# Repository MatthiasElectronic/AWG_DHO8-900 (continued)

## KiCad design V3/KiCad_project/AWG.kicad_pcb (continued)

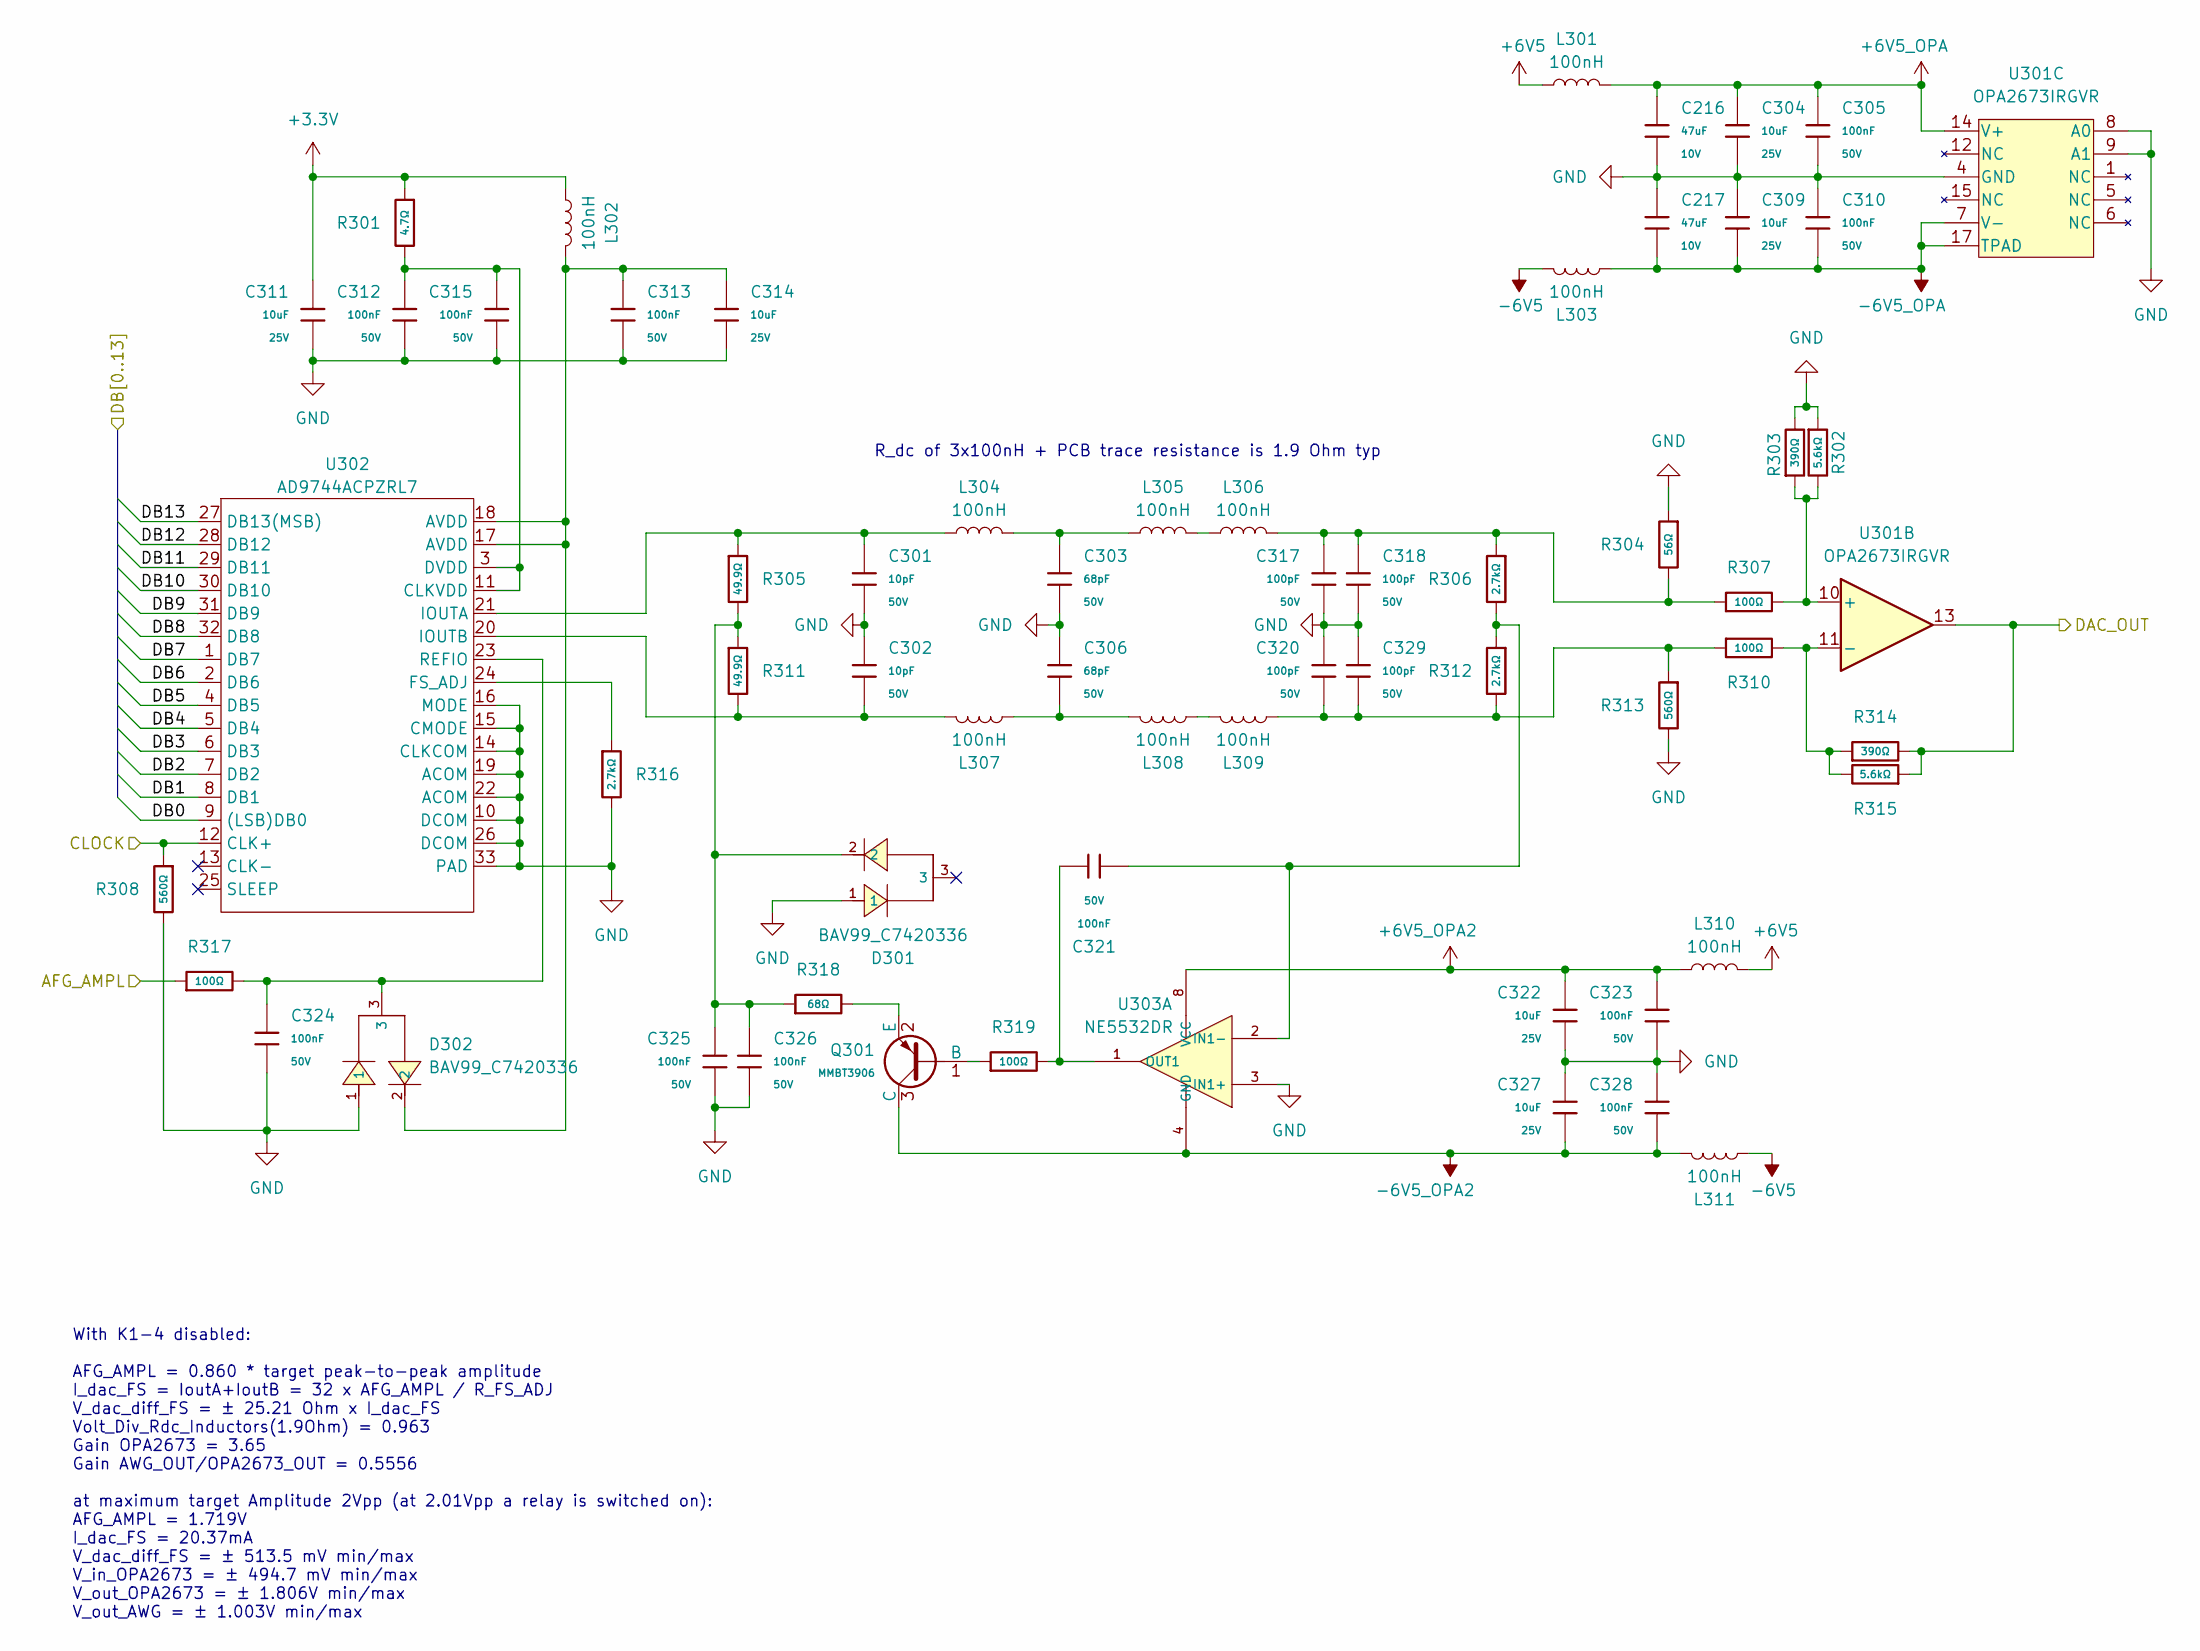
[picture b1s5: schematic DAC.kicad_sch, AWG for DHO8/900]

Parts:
C216, C217: 47uF; C_1206; Voltage Rated 10V; Tolerance ±20%; Part CL31A476MPHNNNE; LCSC C96123
C301, C302: 10pF; C_0603; Voltage Rated 50V; Tolerance ±5%; Part CL10C100JB8NNNC; LCSC C1634
C303, C306: 68pF; C_0603; Voltage Rated 50V; Tolerance ±5%; Part CL10C680JB8NNNC; LCSC C28262
C304, C309, C311, C314, C322, C327: 10uF; C_0805; Voltage Rated 25V; Tolerance ±10%; Part CL21A106KAYNNNE; LCSC C15850
C305, C310, C312, C313, C315, C321, C323, C324, C325, C326, C328: 100nF; C_0603; Voltage Rated 50V; Tolerance ±10%; Part CC0603KRX7R9BB104; LCSC C14663
C317, C318, C320, C329: 100pF; C_0603; Voltage Rated 50V; Tolerance ±5%; Part CL10C101JB8NNNC; LCSC C14858
D301, D302: BAV99_C7420336; SOT-23-3_L2.9-W1.3-P1.90-LS2.4-BR; Reverse Voltage (Vr) 100V; Forward Voltage (Vf@If) 1.25V@150mA; Part BAV99; LCSC C7420336
L301, L302, L303, L304, L305, L306, L307, L308, L309, L310, L311: 100nH; L_0603; LCSC C98088
Q301: MMBT3906; Q_SOT-23; Part MMBT3906; LCSC C7420354
R301: 4.7Ω; R_0603; Overload Voltage (Max) 75V; Tolerance ±1%; Part 0603WAF470KT5E; LCSC C23164
R302, R315: 5.6kΩ; R_0603; Overload Voltage (Max) 75V; Tolerance ±1%; Part 0603WAF5601T5E; LCSC C23189
R303, R314: 390Ω; R_0603; Overload Voltage (Max) 75V; Tolerance ±1%; Part 0603WAF3900T5E; LCSC C23151
R304: 56Ω; R_0603; Overload Voltage (Max) 75V; Tolerance ±1%; Part 0603WAF560JT5E; LCSC C25196
R305, R311: 49.9Ω; R_0603; Overload Voltage (Max) 75V; Tolerance ±1%; Part 0603WAF499JT5E; LCSC C23185
R306, R312, R316: 2.7kΩ; R_0603; Overload Voltage (Max) 75V; Tolerance ±1%; Part 0603WAF2701T5E; LCSC C13167
R307, R310, R317, R319: 100Ω; R_0603; Overload Voltage (Max) 75V; Tolerance ±1%; Part 0603WAF1000T5E; LCSC C22775
R308, R313: 560Ω; R_0603; Overload Voltage (Max) 75V; Tolerance ±1%; Part 0603WAF5600T5E; LCSC C23204
R318: 68Ω; R_0603; Overload Voltage (Max) 75V; Tolerance ±1%; Part 0603WAF680JT5E; LCSC C27592
U301: OPA2673IRGVR; Texas_RSA_VQFN-16-1EP_4x4mm_P0.65mm_EP2.7x2.7mm; LCSC C1848168
U302: AD9744ACPZRL7; LFCSP-32_L5.0-W5.0-P0.50-BL-EP3.1; Manufacturer Part AD9744ACPZRL7; LCSC Part Name AD9744ACPZRL7
U303: NE5532DR; SOIC-8_L4.9-W3.9-P1.27-LS6.0-BL; Part NE5532DR; LCSC C7426

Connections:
+3.3V: C311.1, L302.1, R301.1; also elsewhere on the board
+6V5: L301.2, L310.1; also elsewhere on the board
+6V5_OPA: C216.2, C304.1, C305.1, L301.1, U301.14 (V+); also elsewhere on the board
+6V5_OPA2: C322.1, C323.1, L310.2, U303.8 (VCC); also elsewhere on the board
-6V5: L303.2, L311.1; also elsewhere on the board
-6V5_OPA: C217.1, C309.2, C310.2, L303.1, U301.7 (V-), U301.17 (TPAD); also elsewhere on the board
-6V5_OPA2: C327.2, C328.2, L311.2, Q301.3 (C), U303.4 (GND); also elsewhere on the board
/AFG_AMPL: R317.1; also elsewhere on the board
/CLOCK: R308.1, U302.12 (CLK+); also elsewhere on the board
/DAC/DAC_OUT: R314.2, R315.1, U301.13; also elsewhere on the board
/DB0: U302.9 ((LSB)DB0); also elsewhere on the board
/DB1: U302.8 (DB1); also elsewhere on the board
/DB2: U302.7 (DB2); also elsewhere on the board
/DB3: U302.6 (DB3); also elsewhere on the board
/DB4: U302.5 (DB4); also elsewhere on the board
/DB5: U302.4 (DB5); also elsewhere on the board
/DB6: U302.2 (DB6); also elsewhere on the board
/DB7: U302.1 (DB7); also elsewhere on the board
/DB8: U302.32 (DB8); also elsewhere on the board
/DB9: U302.31 (DB9); also elsewhere on the board
/DB10: U302.30 (DB10); also elsewhere on the board
/DB11: U302.29 (DB11); also elsewhere on the board
/DB12: U302.28 (DB12); also elsewhere on the board
/DB13: U302.27 (DB13(MSB)); also elsewhere on the board
GND: C216.1, C217.2, C301.2, C302.1, C303.2, C304.2, C305.2, C306.1, C309.1, C310.1, C311.2, C312.2, C313.2, C314.2, C315.2, C317.2, C318.2, C320.1, C322.2, C323.2, C324.2, C325.2, C326.2, C327.1, C328.1, C329.1, D301.1, D302.1, R302.1, R303.2, R304.1, R308.2, R313.2, R316.2, U301.4 (GND), U301.8 (A0), U301.9 (A1), U302.10 (DCOM), U302.14 (CLKCOM), U302.15 (CMODE), U302.16 (MODE), U302.19 (ACOM), U302.22 (ACOM), U302.26 (DCOM), U302.33 (PAD), U303.3 (IN1+); also elsewhere on the board
unnamed: C303.1, L304.2, L305.1
unnamed: C306.2, L307.2, L308.1
unnamed: C313.1, C314.1, D302.2, L302.2, U302.17 (AVDD), U302.18 (AVDD)
unnamed: C317.1, C318.1, L306.2, R304.2, R306.1, R307.1
unnamed: C320.2, C329.2, L309.2, R310.1, R312.2, R313.1
unnamed: C325.1, C326.1, D301.2, R305.2, R311.1, R318.1
unnamed: L305.2, L306.1
unnamed: L308.2, L309.1
unnamed: Q301.1 (B), R319.1
unnamed: Q301.2 (E), R318.2
unnamed: R302.2, R303.1, R307.2, U301.10 (+)
unnamed: R310.2, R314.1, R315.2, U301.11 (-)
unnamed: C312.1, C315.1, R301.2, U302.3 (DVDD), U302.11 (CLKVDD)
unnamed: R316.1, U302.24 (FS_ADJ)
unnamed: C301.1, L304.1, R305.1, U302.21 (IOUTA)
unnamed: C302.2, L307.1, R311.2, U302.20 (IOUTB)
unnamed: C324.1, D302.3, R317.2, U302.23 (REFIO)
unnamed: C321.2, R306.2, R312.1, U303.2 (IN1-)
unnamed: C321.1, R319.2, U303.1 (OUT1)

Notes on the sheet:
With K1-4 disabled: AFG_AMPL = 0.860 * target peak-to-peak amplitude I_dac_FS = IoutA+IoutB = 32 x AFG_AMPL / R_FS_ADJ V_dac_diff_FS = ± 25.21 Ohm x I_dac_FS Volt_Div_Rdc_Inductors(1.9Ohm) = 0.963 Gain OPA2673 = 3.65 Gain AWG_OUT/OPA2673_OUT = 0.5556 at maximum target Amplitude 2Vpp (at 2.01Vpp a r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
R_dc of 3x100nH + PCB trace resistance is 1.9 Ohm typ

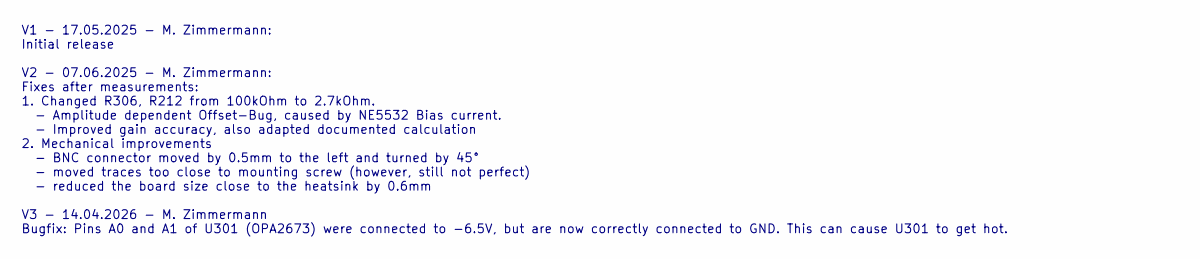
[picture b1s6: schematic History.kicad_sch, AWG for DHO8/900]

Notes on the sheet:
V1 - 17.05.2025 - M. Zimmermann: Initial release V2 - 07.06.2025 - M. Zimmermann: Fixes after measurements: 1. Changed R306, R212 from 100kOhm to 2.7kOhm. - Amplitude dependent Offset-Bug, caused by NE5532 Bias current. - Improved gain accuracy, also adapted documented calculation 2. Mechanical imp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

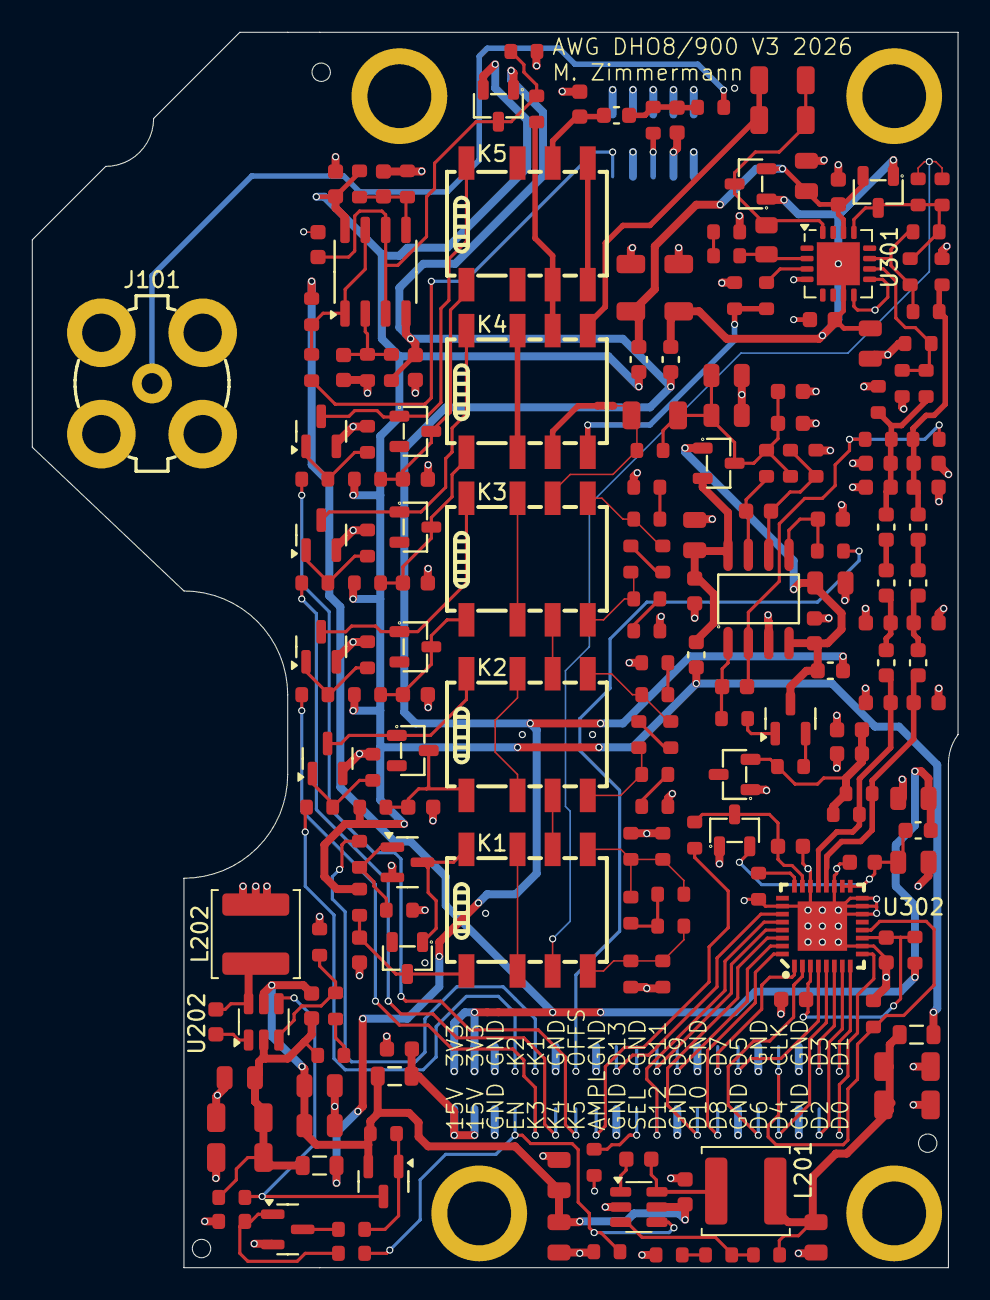
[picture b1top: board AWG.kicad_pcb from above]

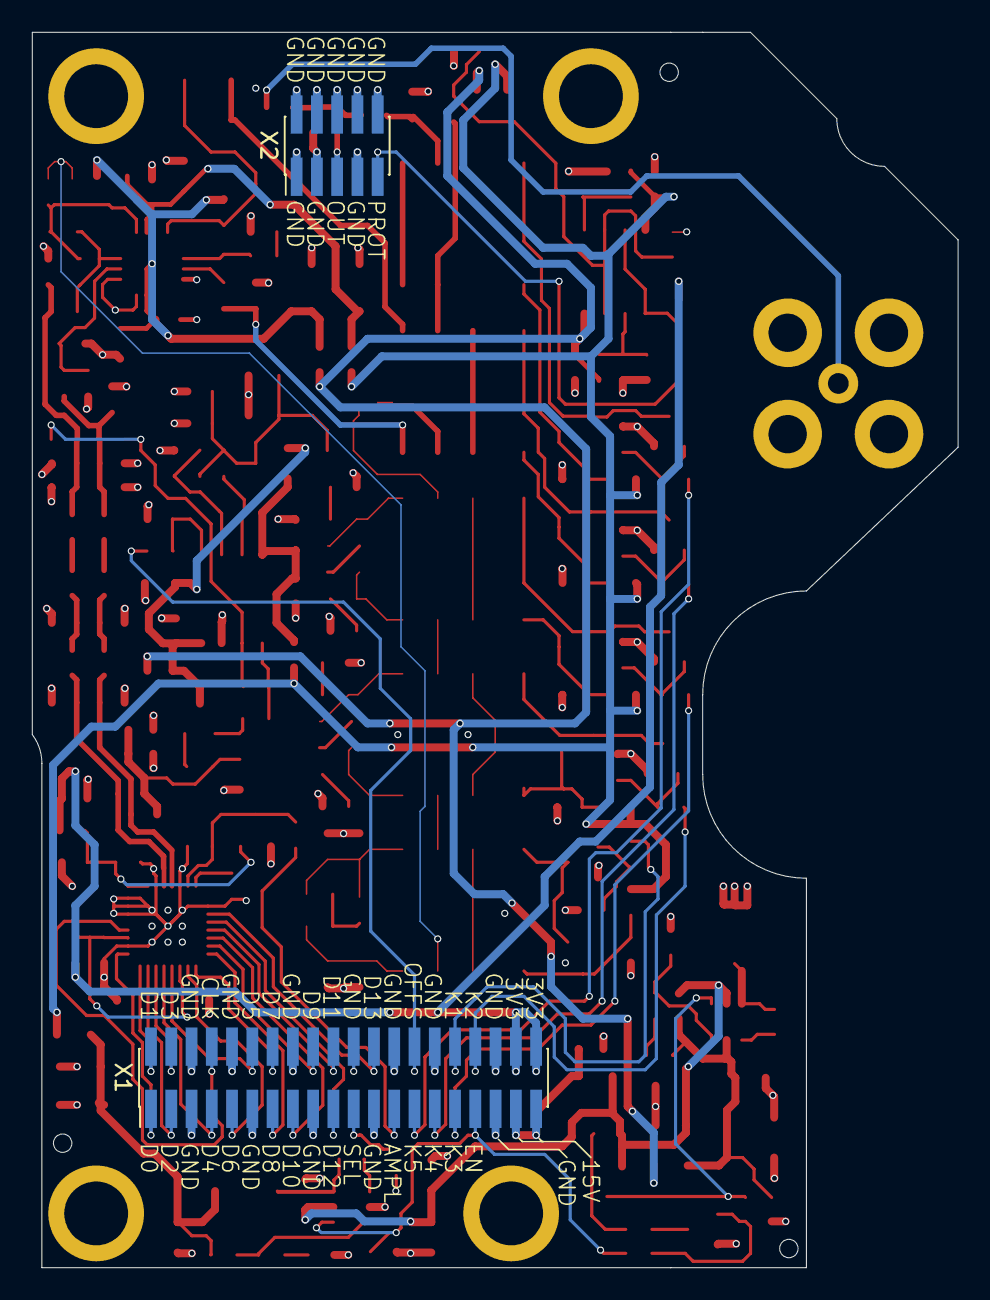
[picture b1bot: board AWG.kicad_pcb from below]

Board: 4 copper layers, 58.0 x 77.4 mm, 208 parts (2 on the bottom side), 126 nets.

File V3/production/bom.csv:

Designator,Footprint,Quantity,Value,LCSC Part #
"C201, C202, C203, C209, C210, C305, C310, C312, C313, C315, C321, C323, C324, C325, C326, C328, C401, C404, C405, C501, C505",C_0603,21,100nF,C14663
"C204, C205, C206, C211, C212, C213, C304, C309, C311, C314, C322, C327, C402, C403",C_0805,14,10uF,C15850
"C207, C208, C214, C215, C216, C217",C_1206,6,47uF,C96123
"C301, C302",C_0603,2,10pF,C1634
"C303, C306",C_0603,2,68pF,C28262
"C317, C318, C320, C329",C_0603,4,100pF,C14858
"C406, C409, C410, C411, C412, C413, C502, C503",C_0603,8,1uF,C15849
"C407, C408, C504",C_0603,3,47pF,C1671
"D301, D302, D401, D402, D403, D404, D405, D406, D407, D408, D501",SOT-23-3_L2.9-W1.3-P1.90-LS2.4-BR,11,BAV99_C7420336,C7420336
"FB201, FB202, FB203",FB_0805,3,~,C1015
J101,BNC_Amphenol_ICC 031-5329-51RFX,1,BNC_Amphenol_ICC 031-5329-51RFX,C5443992
"K1, K2, K3, K4, K5",RELAY-SMD_G6K-2F-X-XX,5,~,C47190
"L201, L202",L_APV_ANR5045,2,22uH,C440232
"L301, L302, L303, L304, L305, L306, L307, L308, L309, L310, L311, L401",L_0603,12,100nH,C98088
"Q201, Q301",Q_SOT-23,2,MMBT3906,C7420354
"Q202, Q401, Q402, Q403, Q404, Q405",Q_SOT-23,6,BC846B,C20069134
"R101, R504",R_0603,2,1kΩ,C21190
R103,R_0603,1,0Ω,C21189
"R201, R207",R_0603,2,24kΩ,C23352
"R202, R205, R206, R210, R212, R435, R436, R440, R441, R442",R_0603,10,22kΩ,C31850
"R203, R208, R209, R408, R433, R434, R437, R438, R439, R502, R507",R_0603,11,3.3kΩ,C22978
"R204, R211, R318, R443, R444, R445, R446, R447",R_0603,8,68Ω,C27592
"R301, R406",R_0603,2,4.7Ω,C23164
"R302, R315",R_0603,2,5.6kΩ,C23189
"R303, R314, R427, R428",R_0603,4,390Ω,C23151
"R304, R430, R431",R_0603,3,56Ω,C25196
"R305, R311",R_0603,2,49.9Ω,C23185
"R306, R312, R316",R_0603,3,2.7kΩ,C13167
"R307, R310, R317, R319, R422, R423, R424, R425",R_0603,8,100Ω,C22775
"R308, R313",R_0603,2,560Ω,C23204
"R401, R419, R420",R_0603,3,4.7kΩ,C23162
"R402, R405, R409",R_0603,3,15Ω,C22810
"R403, R505, R508",R_0603,3,100kΩ,C25803
R404,R_0805,1,270Ω,C17590
R407,R_0603,1,4.3kΩ,C23159
"R410, R413",R_1206,2,100Ω,C17901
"R414, R415, R416, R417",R_0603,4,10Ω,C22859
"R418, R421, R432, R460",R_0603,4,180Ω,C22828
R426,R_0603,1,47Ω,C23182
R429,R_0603,1,6.8kΩ,C23212
R455,R_0603,1,82Ω,C23255
R457,R_1206,1,120Ω,C17909
R458,R_0603,1,1.8kΩ,C4177
"R501, R506",R_0603,2,3.9kΩ,C23018
R503,R_0603,1,5.1kΩ,C23186
"U201, U202",SOT-23-6,2,LMR54406FDBVR,C3193129
U301,Texas_RSA_VQFN-16-1EP_4x4mm_P0.65mm_EP2.7x2.7mm,1,OPA2673IRGVR,C1848168
U302,LFCSP-32_L5.0-W5.0-P0.50-BL-EP3.1,1,AD9744ACPZRL7,C514295
U303,SOIC-8_L4.9-W3.9-P1.27-LS6.0-BL,1,NE5532DR,C7426
U501,SOIC-8_3.9x4.9mm_P1.27mm,1,LM393DR2G,C7955
X1,PinHeader_2x20_P1.27mm_Vertical_SMD,1,Conn_02x20_1.27mm_SMD_Header_M,C2881925
X2,PinHeader_2x05_P1.27mm_Vertical_SMD,1,Conn_02x05_1.27mm_SMD_Header_M,C2881910

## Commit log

2025-06-07 Initial commit, V1 and V2
    Version 1: ordered and tested, but contains bugs (see history in V2 schematic)
    Version 2: bugs from V1 fixed, but new Gerber files are not tested
2025-06-14 Update README.md, corrected sample frequency
2025-06-29 Update README.md: Removed version resistor requirement
2025-07-13 Update README.md
    added link to youtube video
2025-07-16 Fix rotation for JLCPCB
    Add `FT Rotation Offset` fields to components that have a wrong
    rotation when ordering from JLCPCB.
2025-08-07 Silkscreen convenience improvements
    * show BNC lug orientation
    * label connectors on bottom layer
2025-09-14 Added ordering number to value of U201, U202 and U302 because it did not appear in schematic.pdf and in bom.csv
2026-04-14 Added V3.
